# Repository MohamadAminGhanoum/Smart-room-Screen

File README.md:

# Smart-room-Screen

When i usually wake up, i usually look on my phone screen to see the clock, and then i open my social media and do other stuff, which i honestly want to prevent. Therefore i have thought to make a e-ink display on the table next to me, so that i can see the clock and weather directly from my bed when i turn on my night light.

## Final look:

## DEMO
https://www.youtube.com/shorts/77qMShZQf_g

Since i made a previous project about automating my room to control, e.g led strip, open/close the curtain and also measure temperature in the room, i am thinking that i can make this hang together with my other smart-home project.  

I started by researching and mostly gained info about the style and how to connect the E-Ink display connector to the esp32. Therefore i began making schematics, and i did have to do some changes midways, because some components that i wanted were not avaliable in lcsc eleectronics. Therefore i had to search for alternatives. 

Note: the firmware right now is untested, i will do an update for the firmware when this gets approved.

How to use this:
-----------------
This is pretty simple to use, after soldering all the parts on the pcb, it is possible to see the board as a devboard, with some additional components, such as the connector for the E-ink display. The code is flashed normally into the board using the usb-c, and then it is possible to make it work over wifi if wanted, or i can also use this with only the sensor, and the time would be saved, since it is connected through a battery.

This project will allow me to see the time, and through the HTU21D, i can see the temperature and humidity in my room. 
(I will somehow try to connect this to one of my previous projects, where i made a mini smart-home, where i controlled the brightness of the LED and automated opening/ closing the Curtain. I will most likely do future updates on that projects so it becomes possible to connect them.)

## The finished schematics:

## The finished PCB looks like this:

The rendering files or CAD files with/without the screen(The screen is the same size, but not the same type as the one in aliexpress):

## BOM (scroll to the right to see the links):

|Id |Designator               |Footprint                            |Quantity|Comment                            |LCSC quantity                           |Price |Link                                                                                                                                                                                                                                                                                                                                             |
|---|-------------------------|-------------------------------------|--------|-----------------------------------|----------------------------------------|------|-------------------------------------------------------------------------------------------------------------------------------------------------------------------------------------------------------------------------------------------------------------------------------------------------------------------------------------------------|
|1  |C1,C2,C4                 |C_0603_1608Metric                    |3       |10uF                               |10                                      |$0.41 |https://www.lcsc.com/product-detail/C342875.html                                                                                                                                                                                                                                                                                                 |
|2  |CR3,CR1,CR2              |CR_R1_00001_PNJ                      |3       |SS2040FL_R1_00001                  |10                                      |$0.65 |https://www.lcsc.com/product-detail/C7320202.html                                                                                                                                                                                                                                                                                                |
|3  |R14                      |R_0805_2012Metric                    |2       |0.47R                              |100                                     |$0.48 |https://www.lcsc.com/product-detail/C2930220.html                                                                                                                                                                                                                                                                                                |
|4  |R8,R7                    |R_0603_1608Metric                    |2       |4.7K                               |100                                     |$0.13 |https://www.lcsc.com/product-detail/C99782.html                                                                                                                                                                                                                                                                                                  |
|5  |C8,C12,C9,C10,C15,C13,C11|C_0603_1608Metric                    |7       |4.7uF, 25V                         |10                                      |$0.16 |https://www.lcsc.com/product-detail/C69335.html                                                                                                                                                                                                                                                                                                  |
|6  |C6,C7,C5,C16             |C_0603_1608Metric                    |4       |100nF                              |100                                     |$0.35 |https://www.lcsc.com/product-detail/C1590.html                                                                                                                                                                                                                                                                                                   |
|7  |J1                       |USB_C_Receptacle_XKB_U262-16XN-4BVC11|2       |USB_C_Receptacle_USB2.0_14P        |5                                       |$0.89 |https://www.lcsc.com/product-detail/C165948.html                                                                                                                                                                                                                                                                                                 |
|8  |SW2                      |SW_SPST_TS-1088-xR020                |2       |reset/boot                         |10                                      |$0.45 |https://www.lcsc.com/product-detail/C2846765.html                                                                                                                                                                                                                                                                                                |
|9  |R11,R12                  |R_0603_1608Metric                    |2       |33R                                |100                                     |$0.10 |https://www.lcsc.com/product-detail/C2909394.html                                                                                                                                                                                                                                                                                                |
|10 |U6                       |XCVR_ESP32-S3-WROOM-1-N4             |2       |ESP32-S3-WROOM-1-N4                |2                                       |$8.85 |https://www.lcsc.com/product-detail/C2913197.html                                                                                                                                                                                                                                                                                                |
|11 |R5                       |R_0603_1608Metric                    |1       |3K                                 |100                                     |$0.10 |https://www.lcsc.com/product-detail/C2907033.html                                                                                                                                                                                                                                                                                                |
|12 |U5                       |QFN100P300X300X100-7N                |1       |HTU21D                             |2                                       |$4.29 |https://www.lcsc.com/product-detail/C83479.html                                                                                                                                                                                                                                                                                                  |
|13 |J2                       |532610271:MOLEX_532610271            |1       |battery connector                  |5                                       |$0.85 |https://www.lcsc.com/product-detail/C177225.html                                                                                                                                                                                                                                                                                                 |
|14 |R10,R13,R4               |R_0603_1608Metric                    |2       |10K                                |100                                     |$0.11 |https://www.lcsc.com/product-detail/C25804.html                                                                                                                                                                                                                                                                                                  |
|15 |S1                       |SW_SLW-66527511-SMT-TR               |1       |SLW-66527511-SMT-TR                |5                                       |$0.39 |https://www.lcsc.com/product-detail/C49023765.html                                                                                                                                                                                                                                                                                               |
|16 |D3,D2                    |LED_0603_1608Metric                  |2       |LED                                |100                                     |$0.58 |https://www.lcsc.com/product-detail/C19171392.html                                                                                                                                                                                                                                                                                               |
|18 |R2,R1                    |R_0603_1608Metric                    |2       |5.1K                               |100                                     |$0.12 |https://www.lcsc.com/product-detail/C23186.html                                                                                                                                                                                                                                                                                                  |
|19 |U4                       |SOT-23-5                             |1       |MCP73831-3-OT                      |3                                       |$2.18 |https://www.lcsc.com/product-detail/C424093.html                                                                                                                                                                                                                                                                                                 |
|20 |J3                       |AMPHENOL_F34G-1A7Q1-E8C24            |1       |F34G-1A7Q1-E8C24                   |5                                       |$0.25 |https://www.lcsc.com/product-detail/C53223239.html                                                                                                                                                                                                                                                                                               |
|21 |R16                      |R_0603_1608Metric                    |1       |1K                                 |100                                     |$0.13 |https://www.lcsc.com/product-detail/C22548.html                                                                                                                                                                                                                                                                                                  |
|22 |D1                       |D_SMA                                |1       |SS14                               |5                                       |$0.61 |https://www.lcsc.com/product-detail/C83852.html                                                                                                                                                                                                                                                                                                  |
|23 |R6                       |R_0603_1608Metric                    |1       |470                                |100                                     |$0.12 |https://www.lcsc.com/product-detail/C23179.html                                                                                                                                                                                                                                                                                                  |
|24 |C14,C17                  |C_0603_1608Metric                    |2       |4.7uF,25V                          |50                                      |$0.44 |https://www.lcsc.com/product-detail/C6119856.html                                                                                                                                                                                                                                                                                                |
|25 |R3                       |R_0603_1608Metric                    |1       |100K                               |100                                     |$0.13 |https://www.lcsc.com/product-detail/C14675.html                                                                                                                                                                                                                                                                                                  |
|26 |L1                       |L_Taiyo-Yuden_MD-4040                |1       |10uH                               |5                                       |$0.89 |https://www.lcsc.com/product-detail/C92966.html                                                                                                                                                                                                                                                                                                  |
|28 |R15                      |R_0603_1608Metric                    |1       |47K                                |100                                     |$0.14 |https://www.lcsc.com/product-detail/C105579.html                                                                                                                                                                                                                                                                                                 |
|29 |U3                       |SON50P200X200X60-9N                  |1       |ADP124ACPZ-3.3-R7                  |3                                       |$4.27 |https://www.lcsc.com/product-detail/C658731.html                                                                                                                                                                                                                                                                                                 |
|30 |R9                       |SOT-323T_ROM                         |1       |RTF025N03TL                        |5                                       |$1.56 |https://www.lcsc.com/product-detail/C3281999.html                                                                                                                                                                                                                                                                                                |
|31 |C3                       |C_0603_1608Metric                    |1       |4.7uF                              |50                                      |$0.28 |https://www.lcsc.com/product-detail/C1705.html                                                                                                                                                                                                                                                                                                   |
|32 |Q2,Q1                    |SOT-23                               |2       |AO3401A                            |20                                      |$0.71 |https://www.lcsc.com/product-detail/C5296722.html                                                                                                                                                                                                                                                                                                |
|33 |U1                       |SOT65P210X110-3N                     |1       |ADM803SAKSZ-REEL                   |5                                       |$0.93 |https://www.lcsc.com/product-detail/C52146012.html                                                                                                                                                                                                                                                                                               |
|34 |E-ink display            |N/A                                  |1       |HINK-E042A31-A1 4.2inch E-Ink      |                                        |$16.00|https://www.aliexpress.com/item/1005006894281685.html?spm=a2g0o.cart.0.0.608738daADq6GB&mp=1&pdp_npi=6%40dis%21USD%21USD%2016.00%21USD%2015.20%21%21USD%2015.20%21%21%21%40211b441e17698975892792130ecd92%2112000038642259216%21ct%21DK%217012912093%21%211%210%21                                                                               |
|35 |803040 LiPo              |N/A                                  |1       |803040 LiPo battery with protection|                                        |$9.35 |https://www.aliexpress.com/item/32583451110.html?spm=a2g0o.cart.0.0.293238daL2KxmU&mp=1&pdp_npi=6%40dis%21USD%21USD%203.47%21USD%203.47%21%21USD%203.47%21%21%21%40211b80d117703247858814903e1024%2158741290093%21ct%21DK%217012912093%21%211%210%21                                                                                             |
|36 |PCB                      |N/A                                  |5       |JLCPCB                             |                                        |$4.00 |                                                                                                                                                                                                                                                                                                                                                 |
|37 |Threaded inserts         |N/A                                  |4       |Aliexpress                         |                                        |$2.19 |https://www.aliexpress.com/item/1005007640664497.html?spm=a2g0o.cart.0.0.6cb038da4XBX2l&mp=1&pdp_npi=6%40dis%21USD%21USD%202.29%21USD%202.19%21%21USD%202.19%21%21%21%40211b80e117714266379736195e7f10%2112000041610082721%21ct%21DK%217012912093%21%211%210%21&pdp_ext_f=%7B%22cart2PdpParams%22%3A%7B%22pdpBusinessMode%22%3A%22retail%22%7D%7D|
|   |                         |                                     |        |                                   |                                        |      |                                                                                                                                                                                                                                                                                                                                                 |
|   |                         |                                     |        |                                   |Total with shipping, 3d printing legion:|$82.01|                                                                                                                                                                                                                                                                                                                                                 |

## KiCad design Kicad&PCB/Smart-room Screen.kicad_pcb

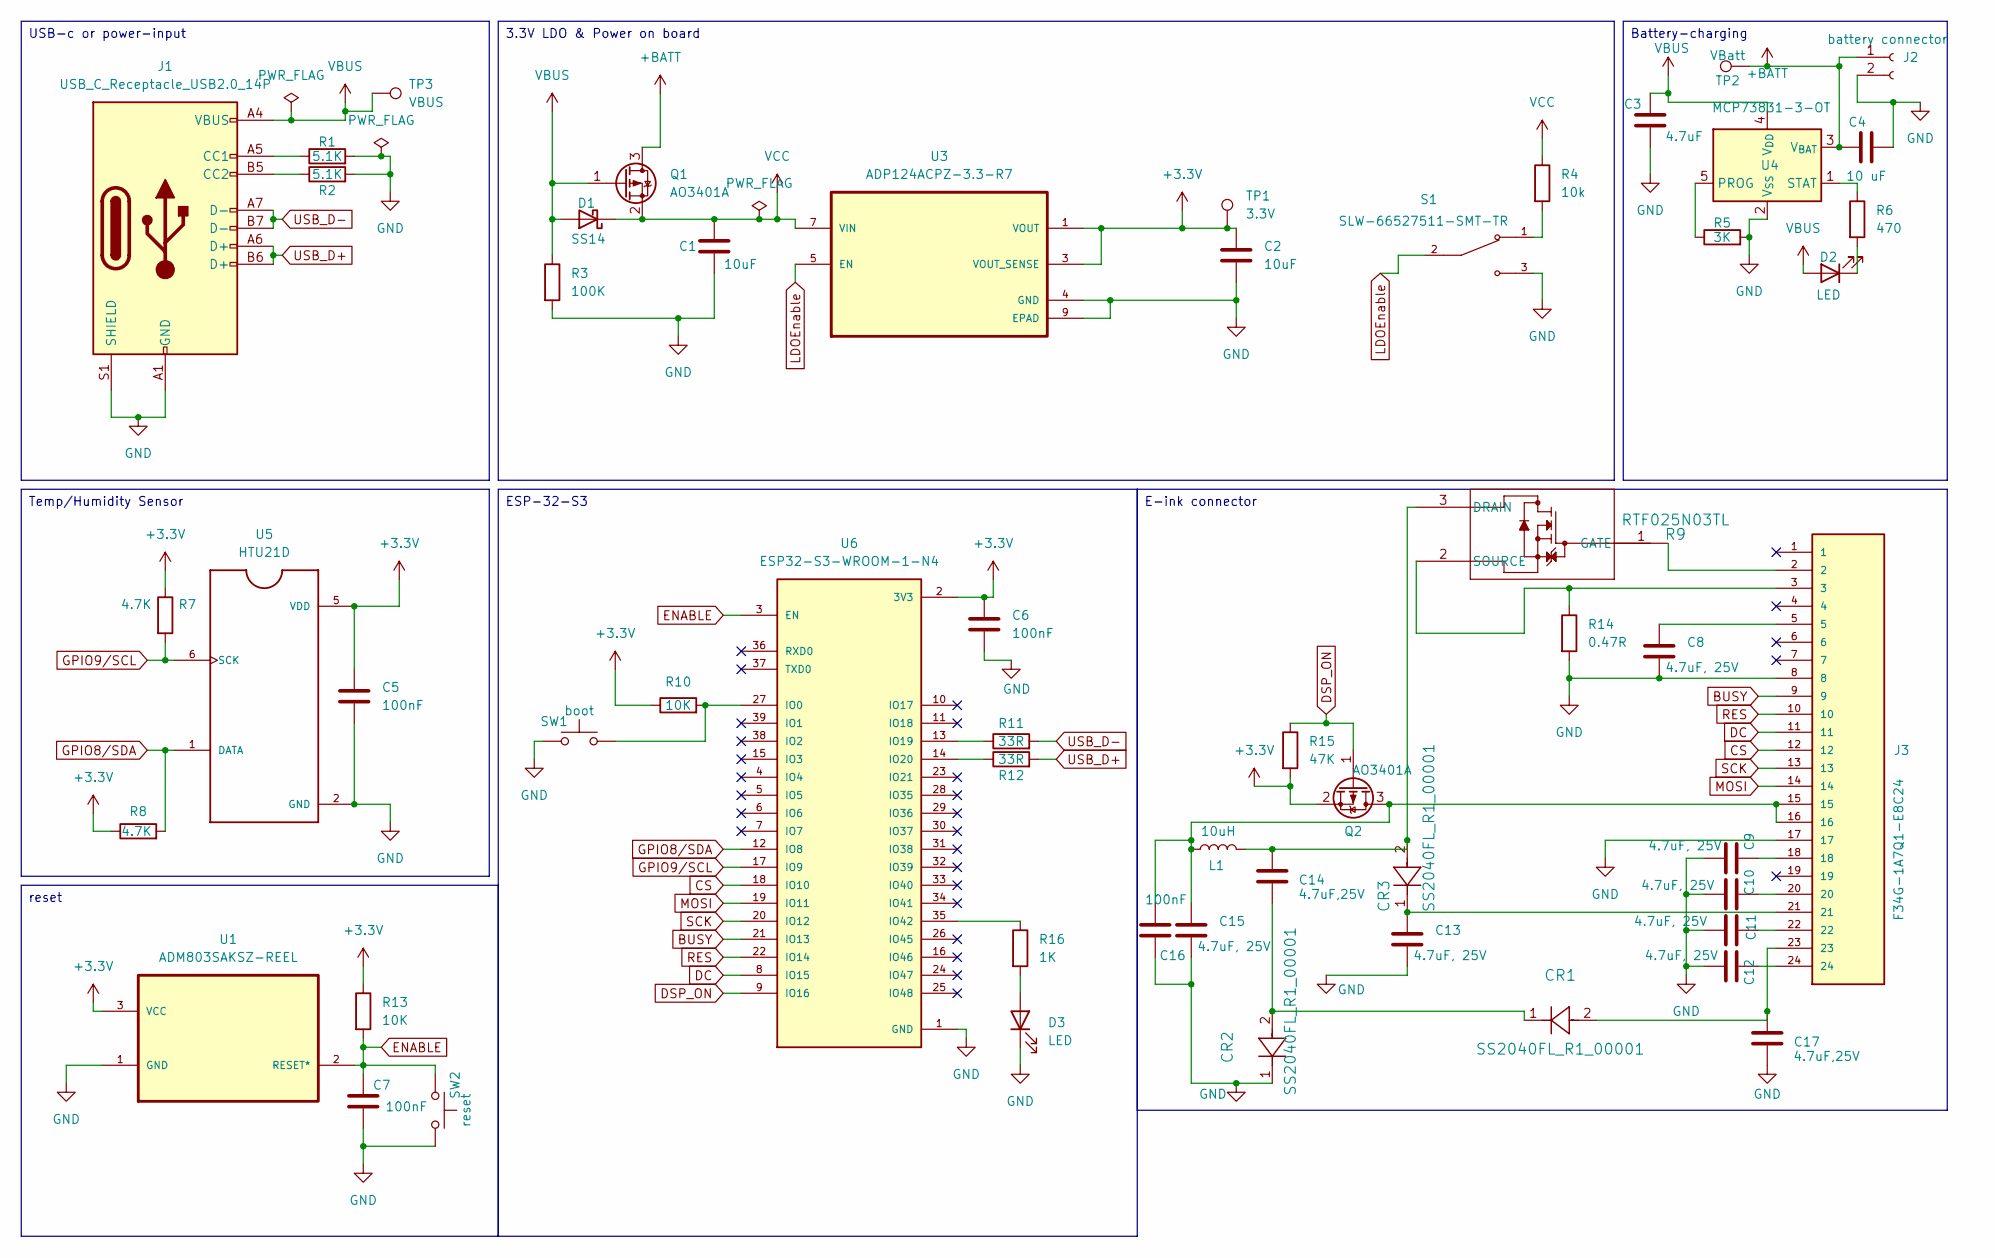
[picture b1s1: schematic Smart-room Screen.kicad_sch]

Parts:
C1, C2: 10uF; C_0603_1608Metric
C3: 4.7uF; C_0603_1608Metric
C4: 10 uF; C_0603_1608Metric
C5, C6, C7, C16: 100nF; C_0603_1608Metric
C8, C9, C10, C11, C12, C13, C15: 4.7uF, 25V; C_0603_1608Metric
C14, C17: 4.7uF,25V; C_0603_1608Metric
CR1, CR2, CR3: SS2040FL_R1_00001; CR_R1_00001_PNJ
D1: SS14; D_SMA
D2, D3: LED; LED_0603_1608Metric
J1: USB_C_Receptacle_USB2.0_14P; USB_C_Receptacle_XKB_U262-16XN-4BVC11
J2: battery connector; JST_PH_S2B-PH-SM4-TB_1x02-1MP_P2.00mm_Horizontal
J3: F34G-1A7Q1-E8C24; AMPHENOL_F34G-1A7Q1-E8C24; PARTREV A
L1: 10uH; L_Taiyo-Yuden_MD-4040
Q1, Q2: AO3401A; SOT-23
R1, R2: 5.1K; R_0603_1608Metric
R3: 100K; R_0603_1608Metric
R4: 10k; R_0603_1608Metric
R5: 3K; R_0603_1608Metric
R6: 470; R_0603_1608Metric
R7, R8: 4.7K; R_0603_1608Metric
R9: RTF025N03TL; SOT-323T_ROM
R10, R13: 10K; R_0603_1608Metric
R11, R12: 33R; R_0603_1608Metric
R14: 0.47R; R_0805_2012Metric
R15: 47K; R_0603_1608Metric
R16: 1K; R_0603_1608Metric
S1: SLW-66527511-SMT-TR; SW_SLW-66527511-SMT-TR; PARTREV 1.01
SW1: boot; SW_SPST_TS-1088-xR020
SW2: reset; SW_SPST_TS-1088-xR020
TP1: 3.3V; TestPoint_Pad_D1.5mm
TP2: VBatt; TestPoint_Pad_D1.5mm
TP3: VBUS; TestPoint_Pad_D1.5mm
U1: ADM803SAKSZ-REEL; SOT65P210X110-3N; MPN ADM803SAKSZ-REEL
U3: ADP124ACPZ-3.3-R7; SON50P200X200X60-9N; PARTREV D
U4: MCP73831-3-OT; SOT-23-5
U5: HTU21D; QFN100P300X300X100-7N
U6: ESP32-S3-WROOM-1-N4; XCVR_ESP32-S3-WROOM-1-N4; PARTREV v1.0

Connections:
+3.3V: C2.1, C5.1, C6.1, Q2.2 (S), R7.1, R8.1, R10.1, R13.1, R15.2, TP1.1, U1.3 (VCC), U3.1 (VOUT), U3.2 (VOUT), U3.3 (VOUT_SENSE), U5.5 (VDD), U6.2 (3V3)
+BATT: C4.1, J2.1, Q1.3 (D), TP2.1, U4.3 (V_{BAT})
BUSY: J3.9, U6.21 (IO13)
CS: J3.12, U6.18 (IO10)
DC: J3.11, U6.8 (IO15)
DSP_ON: Q2.1 (G), R15.1, U6.9 (IO16)
ENABLE: C7.1, R13.2, SW2.1, U1.2 (RESET*), U6.3 (EN)
GND: C1.2, C2.2, C3.1, C4.2, C5.2, C6.2, C7.2, C8.1, C9.2, C10.2, C11.2, C12.2, C13.1, C15.1, C16.2, C17.2, CR2.1, D3.1 (K), J1.A1 (GND), J1.A12 (GND), J1.B1 (GND), J1.B12 (GND), J1.S1 (SHIELD), J2.2, J3.8, J3.17, R1.2, R2.2, R3.2, R5.2, R14.2, S1.3, SW1.1, SW2.2, U1.1 (GND), U3.4 (GND), U3.9 (EPAD), U4.2 (V_{SS}), U5.2 (GND), U5.PAD (GND), U6.1 (GND), U6.40 (GND), U6.41_1 (GND), U6.41_2 (GND), U6.41_3 (GND), U6.41_4 (GND), U6.41_5 (GND), U6.41_6 (GND), U6.41_7 (GND), U6.41_8 (GND), U6.41_9 (GND), U6.41_10, U6.41_11, U6.41_12, U6.41_13, U6.41_14, U6.41_15, U6.41_16, U6.41_17, U6.41_18, U6.41_19, U6.41_20, U6.41_21
GPIO8/SDA: R8.2, U5.1 (DATA), U6.12 (IO8)
GPIO9/SCL: R7.2, U5.6 (SCK), U6.17 (IO9)
LDOEnable: S1.2, U3.5 (EN)
MOSI: J3.14, U6.19 (IO11)
unnamed: C8.2, J3.5
unnamed: C9.1, J3.18
unnamed: C10.1, J3.20
unnamed: C11.1, J3.22
unnamed: C12.1, J3.24
unnamed: C13.2, CR3.1, J3.21
unnamed: C14.2, CR1.1, CR2.2
unnamed: C17.1, CR1.2, J3.23
unnamed: D2.1 (K), R6.2
unnamed: D3.2 (A), R16.2
unnamed: J1.A5 (CC1), R1.1
unnamed: J1.B5 (CC2), R2.1
unnamed: C15.2, C16.1, J3.15, J3.16, L1.1, Q2.3 (D)
unnamed: R4.2, S1.1
unnamed: C14.1, CR3.2, L1.2, R9.3 (DRAIN)
unnamed: J3.2, R9.1 (GATE)
unnamed: J3.3, R9.2 (SOURCE), R14.1
unnamed: R5.1, U4.5 (PROG)
unnamed: R6.1, U4.1 (STAT)
unnamed: R10.2, SW1.2, U6.27 (IO0)
unnamed: R11.1, U6.13 (IO19)
unnamed: R12.1, U6.14 (IO20)
unnamed: R16.1, U6.35 (IO42)
RES: J3.10, U6.22 (IO14)
SCK: J3.13, U6.20 (IO12)
USB_D+: J1.A6 (D+), J1.B6 (D+), R12.2
USB_D-: J1.A7 (D-), J1.B7 (D-), R11.2
VBUS: C3.2, D1.2 (A), D2.2 (A), J1.A4 (VBUS), J1.A9 (VBUS), J1.B4 (VBUS), J1.B9 (VBUS), Q1.1 (G), R3.1, TP3.1, U4.4 (V_{DD})
VCC: C1.1, D1.1 (K), Q1.2 (S), R4.1, U3.7 (VIN), U3.8 (VIN)

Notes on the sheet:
3.3V LDO & Power on board
USB-c or power-input
ESP-32-S3
Battery-charging
Temp/Humidity Sensor
E-ink connector
reset

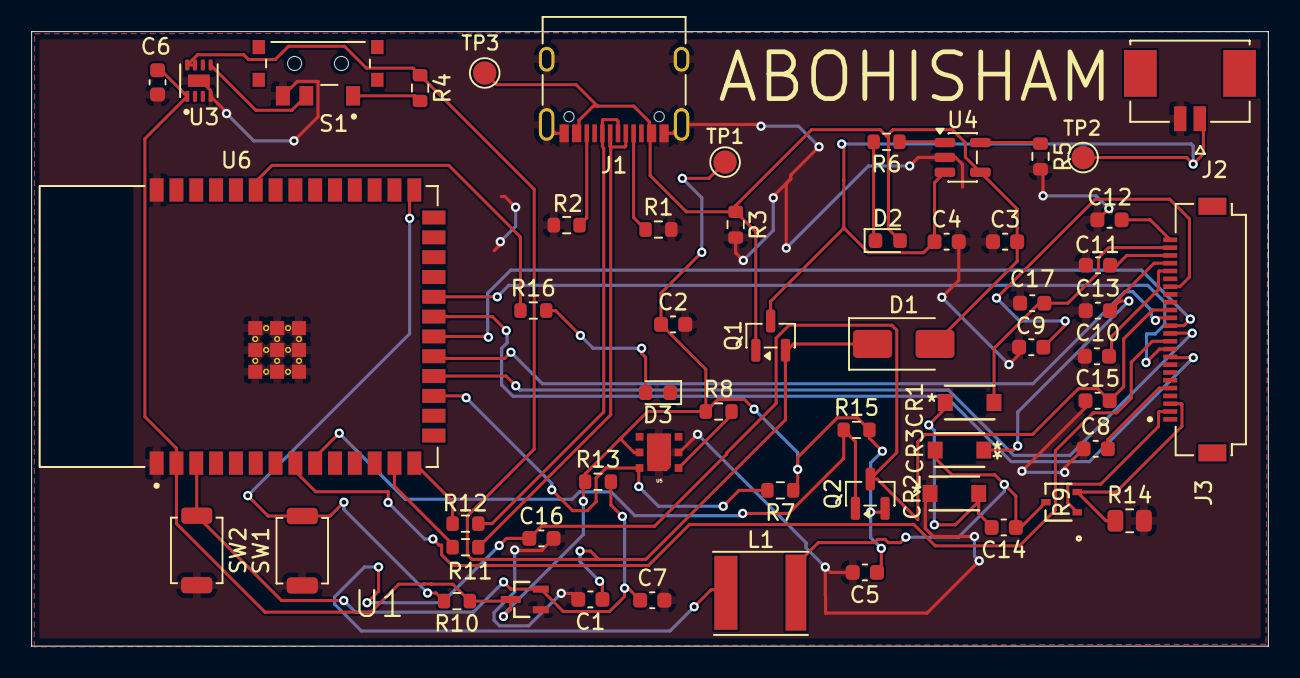
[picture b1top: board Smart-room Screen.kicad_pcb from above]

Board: 2 copper layers, 79.2 x 39.4 mm, 56 parts (0 on the bottom side), 41 nets.

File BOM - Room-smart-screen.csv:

Id,Designator,Footprint,Quantity,Comment,LCSC quantity,Price,Link
1,"C1,C2,C4",C_0603_1608Metric,3,10uF,10,$0.41,https://www.lcsc.com/product-detail/C342875.html
2,"CR3,CR1,CR2",CR_R1_00001_PNJ,3,SS2040FL_R1_00001,10,$0.65,https://www.lcsc.com/product-detail/C7320202.html
3,R14,R_0805_2012Metric,2,0.47R,100,$0.48,https://www.lcsc.com/product-detail/C2930220.html
4,"R8,R7",R_0603_1608Metric,2,4.7K,100,$0.13,https://www.lcsc.com/product-detail/C99782.html
5,"C8,C12,C9,C10,C15,C13,C11",C_0603_1608Metric,7,"4.7uF, 25V",10,$0.16,https://www.lcsc.com/product-detail/C69335.html
6,"C6,C7,C5,C16",C_0603_1608Metric,4,100nF,100,$0.35,https://www.lcsc.com/product-detail/C1590.html
7,J1,USB_C_Receptacle_XKB_U262-16XN-4BVC11,2,USB_C_Receptacle_USB2.0_14P,5,$0.89,https://www.lcsc.com/product-detail/C165948.html
8,SW2,SW_SPST_TS-1088-xR020,2,reset/boot,10,$0.45,https://www.lcsc.com/product-detail/C2846765.html
9,"R11,R12",R_0603_1608Metric,2,33R,100,$0.10,https://www.lcsc.com/product-detail/C2909394.html
10,U6,XCVR_ESP32-S3-WROOM-1-N4,2,ESP32-S3-WROOM-1-N4,2,$8.85,https://www.lcsc.com/product-detail/C2913197.html
11,R5,R_0603_1608Metric,1,3K,100,$0.10,https://www.lcsc.com/product-detail/C2907033.html
12,U5,QFN100P300X300X100-7N,1,HTU21D,2,$4.29,https://www.lcsc.com/product-detail/C83479.html
13,J2,SW_B3U-1000P,1,battery connector,5,$0.64,https://www.lcsc.com/product-detail/C5251182.html
14,"R10,R13,R4",R_0603_1608Metric,2,10K,100,$0.11,https://www.lcsc.com/product-detail/C25804.html
15,S1,SW_SLW-66527511-SMT-TR,1,SLW-66527511-SMT-TR,5,$0.39,https://www.lcsc.com/product-detail/C49023765.html
16,"D3,D2",LED_0603_1608Metric,2,LED,100,$0.58,https://www.lcsc.com/product-detail/C19171392.html
18,"R2,R1",R_0603_1608Metric,2,5.1K,100,$0.12,https://www.lcsc.com/product-detail/C23186.html
19,U4,SOT-23-5,1,MCP73831-3-OT,3,$2.18,https://www.lcsc.com/product-detail/C424093.html
20,J3,AMPHENOL_F34G-1A7Q1-E8C24,1,F34G-1A7Q1-E8C24,5,$0.25,https://www.lcsc.com/product-detail/C53223239.html
21,R16,R_0603_1608Metric,1,1K,100,$0.13,https://www.lcsc.com/product-detail/C22548.html
22,D1,D_SMA,1,SS14,5,$0.61,https://www.lcsc.com/product-detail/C83852.html
23,R6,R_0603_1608Metric,1,470,100,$0.12,https://www.lcsc.com/product-detail/C23179.html
24,"C14,C17",C_0603_1608Metric,2,"4.7uF,25V",50,$0.44,https://www.lcsc.com/product-detail/C6119856.html
25,R3,R_0603_1608Metric,1,100K,100,$0.13,https://www.lcsc.com/product-detail/C14675.html
26,L1,L_Taiyo-Yuden_MD-4040,1,10uH,5,$0.89,https://www.lcsc.com/product-detail/C92966.html
28,R15,R_0603_1608Metric,1,47K,100,$0.14,https://www.lcsc.com/product-detail/C105579.html
29,U3,SON50P200X200X60-9N,1,ADP124ACPZ-3.3-R7,3,$4.27,https://www.lcsc.com/product-detail/C658731.html
30,R9,SOT-323T_ROM,1,RTF025N03TL,5,$1.56,https://www.lcsc.com/product-detail/C3281999.html
31,C3,C_0603_1608Metric,1,4.7uF,50,$0.28,https://www.lcsc.com/product-detail/C1705.html
32,"Q2,Q1",SOT-23,2,AO3401A,20,$0.71,https://www.lcsc.com/product-detail/C5296722.html
33,U1,SOT65P210X110-3N,1,ADM803SAKSZ-REEL,5,$0.93,https://www.lcsc.com/product-detail/C52146012.html
34,E-ink display,N/A,1,HINK-E042A31-A1 4.2inch E-Ink,,$16.00,https://www.aliexpress.com/item/1005006894281685.html?spm=a2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
35,803040 LiPo,N/A,1,803040 LiPo battery with protection,,$9.35,https://www.aliexpress.com/item/32583451110.html?spm=a2g0o.c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
36,PCB,N/A,5,JLCPCB,,$4.00,

,,,,,Total with shipping:,$74.89,

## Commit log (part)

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2026-01-25 Rename Smart-room Screen.kicad_dru to Kicad&PCB/Smart-room Screen.kicad_dru
2026-01-25 Rename Smart-room Screen.kicad_pcb to Kicad&PCB/Smart-room Screen.kicad_pcb
2026-01-25 Rename Smart-room Screen.kicad_prl to Kicad&PCB/Smart-room Screen.kicad_prl
2026-01-25 Rename Smart-room Screen.kicad_pro to Kicad&PCB/Smart-room Screen.kicad_pro
2026-01-25 Rename Smart-room Screen.kicad_sch to Kicad&PCB/Smart-room Screen.kicad_sch
2026-01-31 Update README with project details and goals
    Expanded project description to clarify the purpose and functionality of the smart room screen.
2026-02-02 Rename Smart-room Screen.step to Smart-room Screen.step
2026-02-02 Update README with project details and schematics
    Added details about the project and schematics.
2026-02-02 Rename Screenshot 2026-01-23 at 23.30.38.png to assets/Screenshot 2026-01-23 at 23.30.38.png
2026-02-02 Update README with finished schematics and PCB images
    Added images of the finished schematics and PCB.
2026-02-02 Update README with BOM and project details
    Added a Bill of Materials (BOM) section with details for components used in the project.
2026-02-02 Fix BOM link and improve README formatting
    Updated the BOM link and corrected formatting issues.
2026-02-02 Revise BOM format and add new components
    Updated BOM table format and added new entries.
2026-02-02 Fix formatting and add BOM section to README
    Updated the README to improve formatting and clarity.
2026-02-05 Update README with rendering and CAD files information
    Added rendering and CAD files section with images.
2026-02-05 Add initial firmware for ESP32 with e-ink display
2026-02-05 Add note on untested firmware and future updates
    Added a note about the untested firmware and plans for an update.
2026-02-05 Rename Assembled with pcb.f3z to F3d or F3z CAD files/Assembled with pcb.f3z
2026-02-05 Revise BOM with new components and pricing
    Updated component list and prices in BOM for Room-smart-screen.
2026-02-18 Add new image to README and update PCB screenshot
2026-02-18 Remove duplicate images from README
    Removed duplicate images from Aliexpres and JLCPCB sections.
2026-02-18 Update README formatting and section headers
2026-02-19 Update README with rendering and CAD file images
    Added images of rendering files and CAD files.
2026-06-25 Clean up README.md by removing BOM cart pictures
    Removed unnecessary BOM cart pictures and cleaned up the formatting.
